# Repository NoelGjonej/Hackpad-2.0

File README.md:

# PCB Design

# Case Design

# XIAO Macropad — KMK Firmware
## Seeeduino XIAO · 6 Keys · EC11E Rotary Encoder · SSD1306 128x32 OLED

---

## Why KMK instead of QMK?

KMK runs on **CircuitPython** — there is no compiling, no toolchain, no flashing.
You just copy files onto the XIAO like a USB drive. Much easier for the XIAO.

---

## Key Layout

```
[ PREV  ] [ PLAY  ] [ NEXT  ]
[ COPY  ] [ PASTE ] [ SNIP  ]
                              Encoder CW  → Volume Up
                              Encoder CCW → Volume Down
                              Encoder Click → Mute / Unmute
```

| Key | Action |
|-----|--------|
| Top-left  | ⏮ Previous Track |
| Top-mid   | ▶ Play / Pause |
| Top-right | ⏭ Next Track |
| Bot-left  | Ctrl+C — Copy |
| Bot-mid   | Ctrl+V — Paste |
| Bot-right | Win+Shift+S — Snipping Tool |
| Encoder CW | 🔊 Volume Up |
| Encoder CCW | 🔉 Volume Down |
| Encoder click | 🔇 Mute / Unmute toggle |

---

## Wiring

### Key Matrix (2 rows × 3 cols, COL2ROW diodes)

```
         COL0(D0)   COL1(D1)   COL2(D2)
ROW0(D3)   PREV       PLAY       NEXT
ROW1(D4)   COPY       PASTE      SNIP
```

Add a 1N4148 diode per switch — cathode (black band) toward the ROW pin.

### EC11E Encoder

| EC11E pin | XIAO pin | Function       |
|-----------|----------|----------------|
| CLK (A)   | D7       | Rotation A     |
| DT  (B)   | D8       | Rotation B     |
| SW        | D6       | Click = Mute   |
| GND       | GND      | Ground         |

Add 10kΩ pull-up resistors on CLK and DT to 3.3V if you get jitter.

### SSD1306 OLED (I2C, 128×32)

| OLED pin | XIAO pin      |
|----------|---------------|
| SDA      | D9  (SDA)     |
| SCL      | D10 (SCL)     |
| VCC      | 3.3V          |
| GND      | GND           |

Default I2C address is 0x3C. If your OLED doesn't appear, try 0x3D in code.py.

---

## Setup Instructions

### Step 1 — Install CircuitPython on the XIAO

1. Download the CircuitPython UF2 for Seeeduino XIAO from:
   https://circuitpython.org/board/seeeduino_xiao/
   (download the latest stable .uf2 file)

2. Double-tap the RST pin on the XIAO — a drive called **XIAO-BOOT** appears on your PC.

3. Drag and drop the `.uf2` file onto that drive.
   The XIAO reboots and a new drive called **CIRCUITPY** appears.

### Step 2 — Install CircuitPython libraries

Download the CircuitPython Library Bundle from:
https://circuitpython.org/libraries

Unzip it. From the `lib/` folder inside, copy these folders/files
into the `lib/` folder on your **CIRCUITPY** drive:

```
adafruit_displayio_ssd1306.mpy
adafruit_display_text/
adafruit_imageload/
kmk/                          ← get this from https://github.com/KMKfw/kmk_firmware
```

To get KMK, download the zip from https://github.com/KMKfw/kmk_firmware
and copy the `kmk/` folder onto CIRCUITPY/lib/.

### Step 3 — Copy your code

Copy these two files from this folder onto the root of **CIRCUITPY**:

```
boot.py   → CIRCUITPY/boot.py
code.py   → CIRCUITPY/code.py
```

Your CIRCUITPY drive should look like:
```
CIRCUITPY/
├── boot.py
├── code.py
└── lib/
    ├── kmk/
    ├── adafruit_displayio_ssd1306.mpy
    ├── adafruit_display_text/
    └── adafruit_imageload/
```

### Step 4 — Done

The XIAO reboots automatically when you save files. Your macropad is ready.
No compiling, no flashing tools needed.

---

## Making changes

To change a key, open `code.py` in any text editor, edit the `keyboard.keymap` list,
and save. The XIAO reboots and picks up the change in a few seconds.

Common keycodes:
```python
KC.LCTL(KC.Z)     # Ctrl+Z  (undo)
KC.LCTL(KC.S)     # Ctrl+S  (save)
KC.LGUI(KC.L)     # Win+L   (lock screen)
KC.PSCR           # Print Screen
KC.TAB, KC.ESC, KC.ENT, KC.BSPC
KC.F1 ... KC.F12
```

---

## Troubleshooting

| Problem | Fix |
|---------|-----|
| CIRCUITPY drive doesn't appear | Double-tap RST faster (within ~500ms) |
| Keys not working | Check diode direction — cathode (black band) toward row pin |
| Encoder jittery | Add 10kΩ pull-ups on CLK and DT to 3.3V |
| OLED blank | Check SDA/SCL wiring; try changing 0x3C to 0x3D in code.py |
| Error on boot | Connect to XIAO via serial (PuTTY / Thonny) to read the error message |

### Reading error messages (very useful for debugging)

Install **Thonny** (free Python IDE): https://thonny.org
Connect to the XIAO's serial port — it shows any Python errors live,
which makes debugging very easy.

---

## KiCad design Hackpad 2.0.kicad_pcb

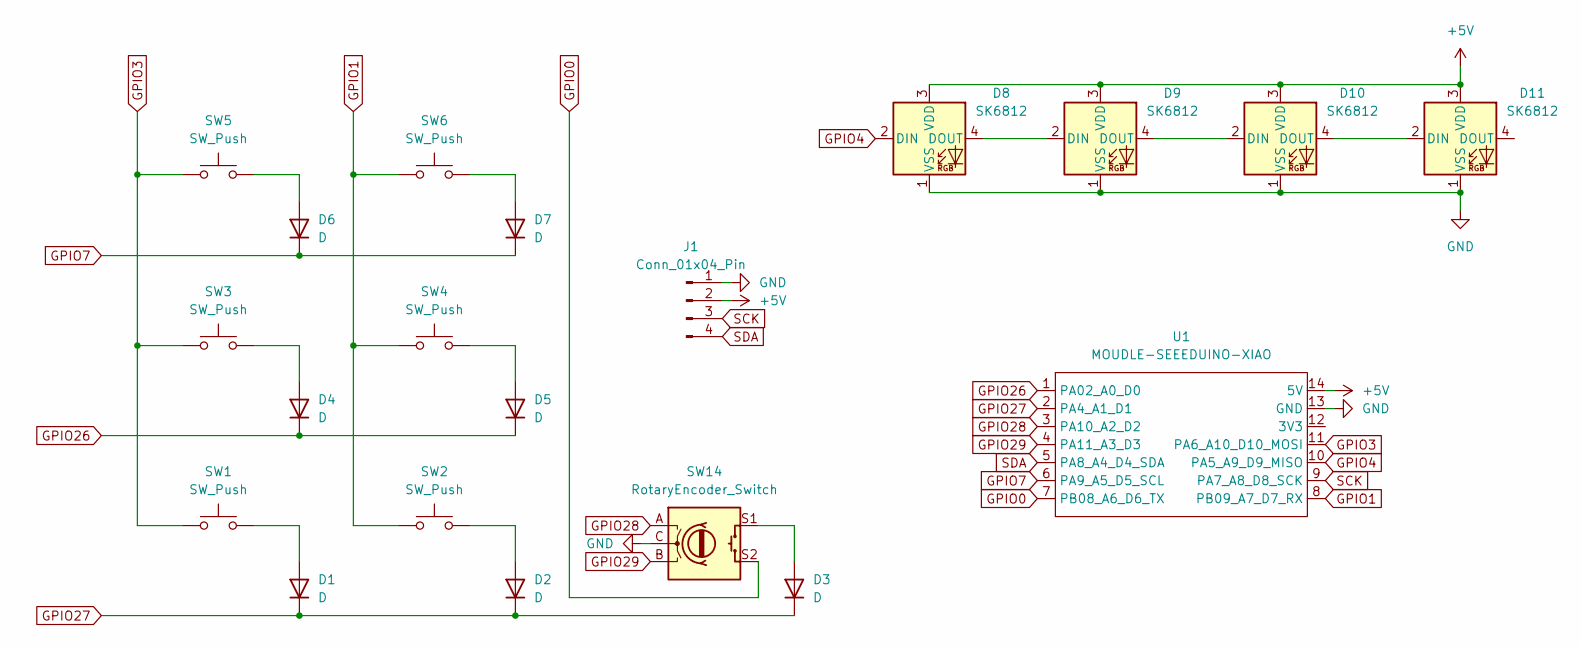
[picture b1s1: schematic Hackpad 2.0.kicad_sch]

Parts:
D1, D2, D3, D4, D5, D6, D7: D; D_DO-35_SOD27_P7.62mm_Horizontal
D8, D9, D10, D11: SK6812; LED_SK6812_PLCC4_5.0x5.0mm_P3.2mm
J1: Conn_01x04_Pin; PinSocket_1x04_P2.54mm_Vertical
SW1, SW2, SW3, SW4, SW5, SW6: SW_Push; SW_Cherry_MX_1.00u_PCB
SW14: RotaryEncoder_Switch; RotaryEncoder_Alps_EC11E-Switch_Vertical_H20mm
U1: MOUDLE-SEEEDUINO-XIAO; XIAO-Generic-Hybrid-14P-2.54-21X17.8MM

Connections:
+5V: D8.3 (VDD), D9.3 (VDD), D10.3 (VDD), D11.3 (VDD), J1.2, U1.14 (5V)
GND: D8.1 (VSS), D9.1 (VSS), D10.1 (VSS), D11.1 (VSS), J1.1, SW14.C, U1.13 (GND)
GPIO0: SW14.S2, U1.7 (PB08_A6_D6_TX)
GPIO1: SW2.1, SW4.1, SW6.1, U1.8 (PB09_A7_D7_RX)
GPIO3: SW1.1, SW3.1, SW5.1, U1.11 (PA6_A10_D10_MOSI)
GPIO4: D8.2 (DIN), U1.10 (PA5_A9_D9_MISO)
GPIO7: D6.1 (K), D7.1 (K), U1.6 (PA9_A5_D5_SCL)
GPIO26: D4.1 (K), D5.1 (K), U1.1 (PA02_A0_D0)
GPIO27: D1.1 (K), D2.1 (K), D3.1 (K), U1.2 (PA4_A1_D1)
GPIO28: SW14.A, U1.3 (PA10_A2_D2)
GPIO29: SW14.B, U1.4 (PA11_A3_D3)
unnamed: D1.2 (A), SW1.2
unnamed: D2.2 (A), SW2.2
unnamed: D3.2 (A), SW14.S1
unnamed: D4.2 (A), SW3.2
unnamed: D5.2 (A), SW4.2
unnamed: D6.2 (A), SW5.2
unnamed: D7.2 (A), SW6.2
unnamed: D8.4 (DOUT), D9.2 (DIN)
unnamed: D9.4 (DOUT), D10.2 (DIN)
unnamed: D10.4 (DOUT), D11.2 (DIN)
SCK: J1.3, U1.9 (PA7_A8_D8_SCK)
SDA: J1.4, U1.5 (PA8_A4_D4_SDA)

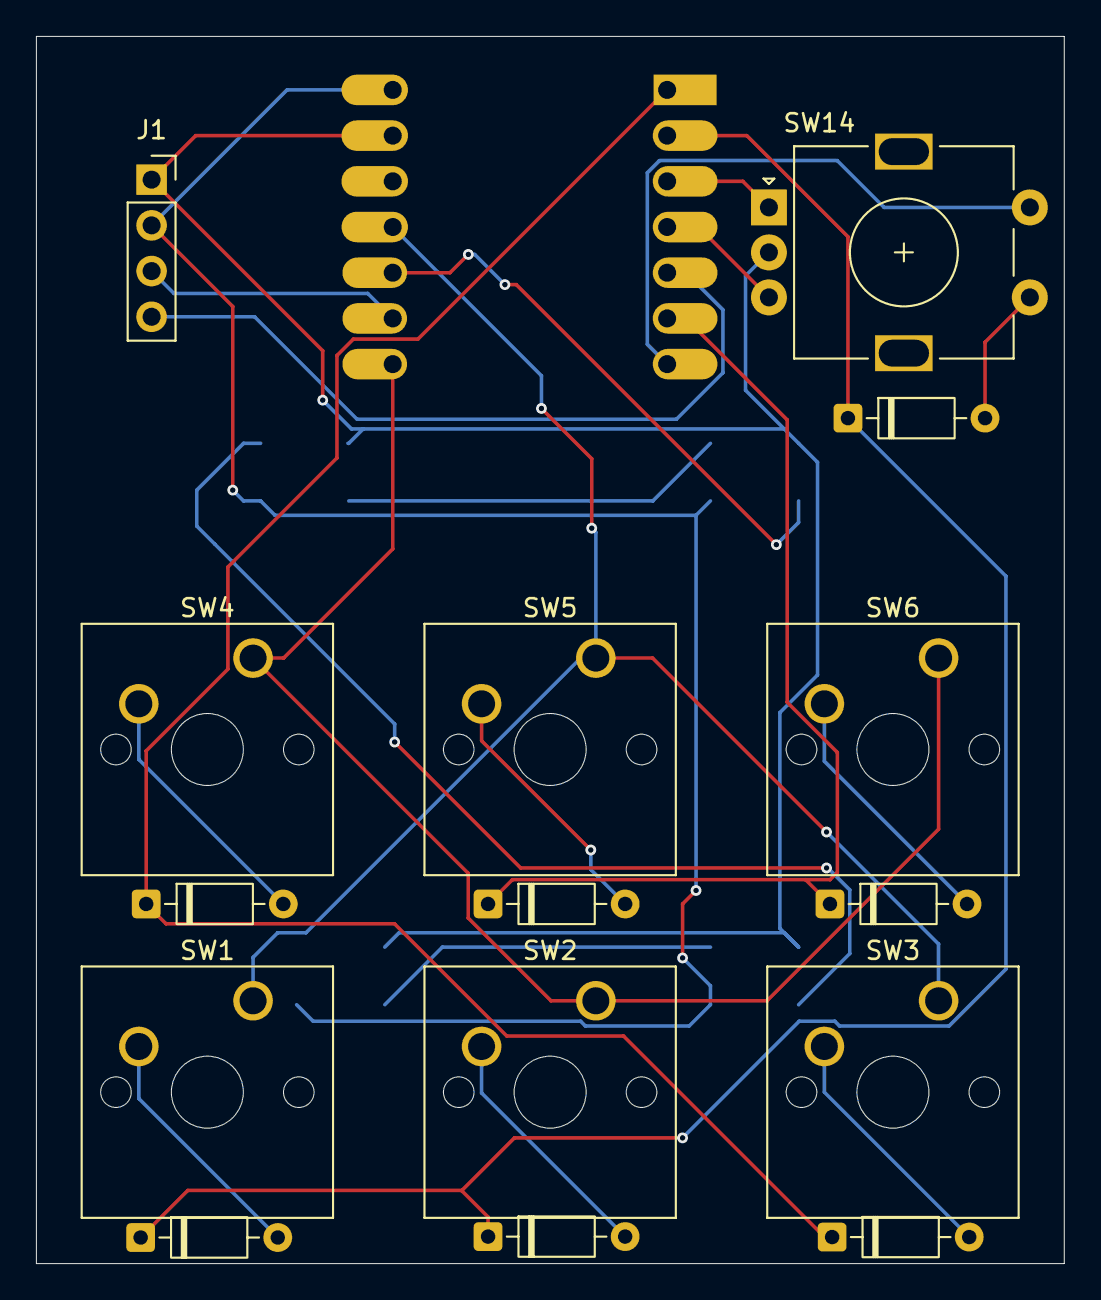
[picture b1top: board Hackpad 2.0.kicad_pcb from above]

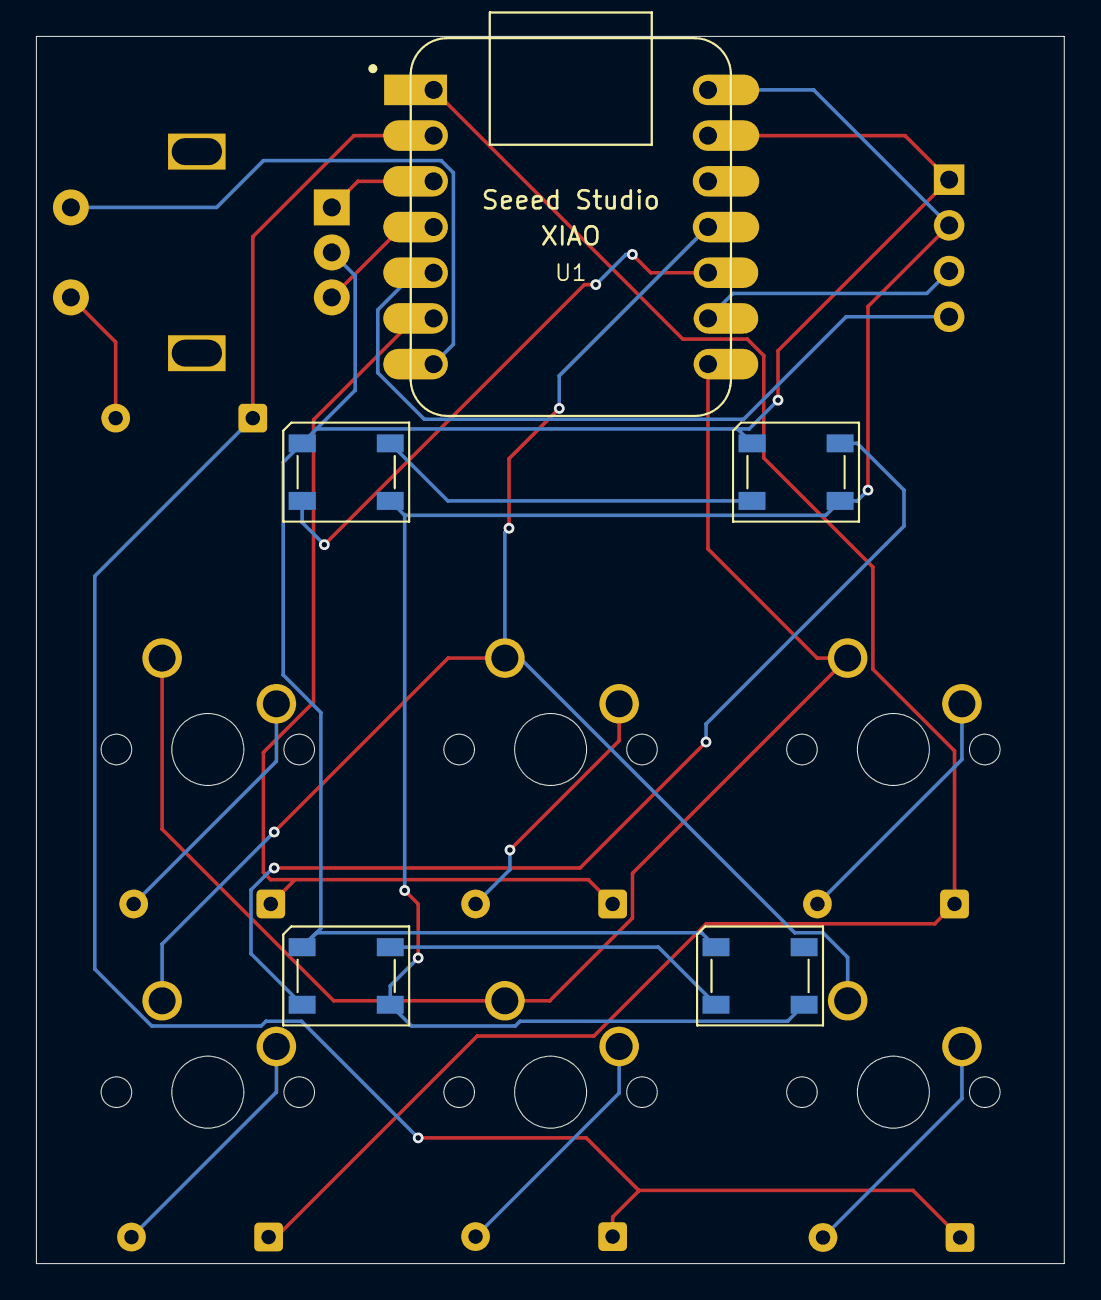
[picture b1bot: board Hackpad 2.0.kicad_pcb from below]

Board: 2 copper layers, 57.1 x 68.2 mm, 20 parts (5 on the bottom side), 23 nets.

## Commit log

2026-04-17 Update README with PCB and Case design sections
    Added sections for PCB and Case design with images.
2026-04-18 Update image in PCB Design section of README
